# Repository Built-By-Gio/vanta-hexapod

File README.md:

# VANTA hexapod

VANTA is my 18-DOF six-legged walking robot: 6 legs with 3 MG995 servos each, printed in PLA on a Bambu A1, wired with Wago connectors and screw terminals so nothing needs soldering. It runs on an ESP32-S3 with two PCA9685 servo drivers and I drive it with an Xbox Wireless controller over Bluetooth (Bluepad32). I designed the servo caps, aluminium-horn brackets, electronics plate, hulls, top deck, riser and camera holder, and wrote the firmware, the MuJoCo simulator, the leg neural network and the assembly guide. The leg and body parts are adapted from an open-source hexapod and reworked for this build (see Credits).

Built by Gio ([Built-By-Gio](https://github.com/Built-By-Gio)).

*VANTA walking and turning on a concrete floor.* [Watch the full walking video (1:55)](media/vanta_walking.mp4)

*The v6 CAD design (Pi-era hull).*

## Status (2026-11-25)

**Done**
- VANTA is fully built and walks on the ESP32-S3 + 2x PCA9685 build, driven from an Xbox controller over Bluetooth.
- Everything in the firmware runs on the robot: tripod walking, turning, crab walking, stand/sit, body lean, height and speed control, and the wave, bow, rear-up and dance moves.
- The learned walk, the injured-leg (5-leg) walks and step climbing run on the robot. I train and develop them in the MuJoCo simulator (`4_SOFTWARE/sim_and_training/`). Full house stairs (about 18 cm) are out of reach.
- The leg neural network (`ik_net.h`) runs on the robot. On 50,000 unseen foot positions, `train_ik.py` reports about 0.5 degrees average joint error.
- The Fusion top deck, riser, camera holder and slotted tall hull (`3_CAD/deck_hull_fusion/`) are printed and on the robot.

**Not done yet**
- Camera: the holder is on the robot (Waveshare ESP32-S3-CAM, OV5640). The camera code is not written yet.
- Carrier PCB (`6_PCB_CARRIER/`): design only, not ordered. It targets the old Raspberry Pi layout.
- Raspberry Pi software (`4_SOFTWARE/hexapod-brain/`): legacy. VANTA started on a Raspberry Pi 4, and I replaced it with the ESP32-S3 before this code ran on the robot.

**Known problems**
- MG995 servos have overheated and failed: one died on the bench and was swapped. Keep a spare or two.
- The assembly guide's pictures show the +1 servo cap; the cap that fits is +2 (1 mm difference, cosmetic).
- `1_PRINT/VANTA_print_MAIN_A1.3mf` was rewritten by a script to 12 plates with +2 caps and has not been re-opened in Bambu Studio since. Check the plates before printing.
- Check the deck fit before printing the files in `3_CAD/deck_hull_fusion/`: the riser columns reach Z 59.9 mm and run 3.2 mm into the deck, and the riser opening covers the end-header servo plugs by 0.5 mm.
- Measure your camera module; the camera holder assumes a module depth of 8.5 mm.
- `3_CAD/VANTA_standing.glb` still shows an older bracket B, horn and caps. The CAD render near the top shows the v6 CAD design with the Pi-era hull, not the robot as it is today.

**Battery:** the robot runs on a 3S LiPo (stop at 10.5 V). The original parts list named a Zeee 2S 5200 mAh XT60 pack. Check that your SBEC and buck converter accept your pack's voltage.

**Still to add**
- How the ESP32-S3 board is mounted and fed 5 V (its ground goes to the 5 V- Wago).
- The script that exports `walk_net.h` (`export_walk.py`), and a note on what `best.npy` holds.

The 5:54 assembly video rendered from the CAD (337 MB) is not in this repo because of its size; its source pipeline is in `7_VIDEO/assembly_video_src/`.

## Photos

| | |
|---|---|
|  |  |
| Electronics plate during the build | Power wiring with Wago connectors |

## What you need

**Electronics and hardware** (from the 2026-11-03 parts list, `BUY_LIST.md`, with the controller changed to the current ESP32 build):

| Item | Qty |
|---|---|
| MG995 servo (plus spares) | 18 |
| ESP32-S3 DevKitC | 1 |
| PCA9685 16-channel servo driver | 2 |
| Xbox Wireless controller (Bluetooth) | 1 |
| 20 A SBEC set to 6.0 V (servo power) | 1 |
| XL4015 buck converter set to 5.1 V (logic, fans) | 1 |
| LiPo with XT60 plug (see the battery note above) | 1 |
| 20 A inline fuse, XT60 rocker switch, XT60 pigtails | 1 each |
| Wago 221 lever connectors, 16 AWG wire, F-F jumpers | as needed |
| 30 cm servo extensions | 6 |
| 30 mm 5 V fans (hull roof) | 2 |
| DaFuRui 25T aluminium disc horns (Ø20 mm, 4x M3 on a 10 mm square) | 18 |
| 623ZZ bearings (3x10x4, not flanged) | 18 |
| M3 heat-set inserts (M3 x L4 x OD5) | 44 |
| M3x6 / M3x8 / M3x10 screws | 28 (+72 for the horns) / 48 / 110 |
| M2.5x6 screws / M2x8 screws with nuts | 12 / 4 |
| Grip tape for the feet, CA glue | |

The main board and drivers need no soldering. The robot weighs about 2.45 kg with the hull (design estimate).

**Printing:** a Bambu A1 (the 3MF files are set up for it), black PLA, and optionally silver PLA with an AMS for the lettering.

**Software:**
- Arduino IDE 2 with the `esp32_bluepad32` board package 4.1.0 (board manager URL: `https://raw.githubusercontent.com/ricardoquesada/esp32-arduino-lib-builder/master/bluepad32_files/package_esp32_bluepad32_index.json`). Bluepad32 comes with this board package.
- Arduino libraries: Adafruit PWM Servo Driver Library 3.0.3 and Adafruit BusIO 1.17.4.
- For the simulator and training: Python 3.13 with `mujoco` (tested with 4.0.0) and `numpy` (tested with 2.5.3).

## How to build / run

1. **Print the fit test first.** Open `1_PRINT/VANTA_print_MAIN_A1.3mf` and print plate 1: one bracket A, one bracket B and one +2 servo cap. Build one joint (guide step 1) and check the cap fits your servo. Cap STLs from +0 to +3 are in `1_PRINT/stl_main/` if yours needs a different size.
2. **Print the rest of the MAIN file.** `1_PRINT/MAIN_plate_layout.png` shows all 12 plates. Infill: femur, tibia, both bracket As, bracket B and the caps at 15% with 4 walls; electronics plate, deck and battery mount at 10% with 2 walls; armour at 5% (it is cosmetic). The hull (`1_PRINT/VANTA_print_COLOR_AMS_A1.3mf`, or a variant from `3_CAD/deck_hull_fusion/deck_out/`) prints upright with tree supports at 10%.
3. **Assemble the mechanics** with `VANTA_assembly_guide.pdf` (rev 9, 33 pages). Each joint: a slip-on cap holds a 623ZZ bearing; an M3x10 axle self-taps through bracket A into the bearing; on the horn side, bracket B sits over the aluminium disc with 4x M3x6. Self-tap holes: drive the screw in once to cut the thread, back it out, then assemble. Wrap grip tape around the bottom 25 mm of each tibia tip as the foot. The guide's Pi wiring and Pi software chapters are legacy; use steps 4 to 8 below for the electronics.
4. **Wire the power.** Battery, switch, 20 A fuse, then a BATT+ Wago that feeds the SBEC and the buck. Both SBEC outputs (6.0 V) go to the green V+ terminals of both PCA9685 boards. The buck output (5.1 V) goes to the 5V+/5V- Wagos. PCA9685 VCC comes from the ESP32's 3.3 V. Never put servo power on a board's 5 V pin.
5. **Wire the drivers to the ESP32-S3.** Driver 1 on `Wire`: SDA GPIO 8, SCL GPIO 9. Driver 2 on `Wire1`: SDA GPIO 4, SCL GPIO 5. Both stay at address 0x40. Plug the servos in as in the table below (`BOARD`/`CH` in `vanta_hexapod_pad.ino`, lines 39-41). Leg names are from the robot's point of view, front = the way it walks with the stick forward.

   | Leg | coxa | femur | tibia |
   |---|---|---|---|
   | front left | driver 2 ch 0 | driver 2 ch 1 | driver 2 ch 2 |
   | middle left | driver 2 ch 4 | driver 2 ch 5 | driver 2 ch 3 |
   | back left | driver 2 ch 7 | driver 2 ch 6 | driver 2 ch 8 |
   | front right | driver 1 ch 0 | driver 1 ch 1 | driver 2 ch 15 |
   | middle right | driver 1 ch 3 | driver 1 ch 4 | driver 1 ch 5 |
   | back right | driver 1 ch 6 | driver 1 ch 7 | driver 1 ch 8 |

   If your wiring differs, edit `BOARD` and `CH`.
6. **Check every servo before walking.** In the Arduino IDE pick board "ESP32S3 Dev Module" and enable "USB CDC On Boot". Upload `5_ELECTRONICS_TEST/esp32s3/servo_finder/servo_finder.ino` to see which channel each servo is on (Serial Monitor 115200, "No line ending"; type `2 6` to wiggle driver 2 channel 6). Then upload `5_ELECTRONICS_TEST/esp32s3/servo_check/servo_check.ino`, which wiggles all 18 joints in order using the same table (`n` next, `b` back, `r` repeat). If the Serial Monitor shows only `ESP-ROM:`, press RST.
7. **Upload the walking firmware.** Open `4_SOFTWARE/esp32_firmware/vanta_hexapod_pad/vanta_hexapod_pad.ino` (keep `ik_net.h` and `walk_net.h` in the same folder) and upload it. Put the robot down sitting: battery on the floor, legs spread in a standing shape.
8. **Calibrate the stand pose.** In the Serial Monitor (115200, "No line ending"): `1`-`6` pick a leg, `c`/`f`/`t` pick a joint, `+`/`-` nudge 10 µs, `]`/`[` nudge 50 µs, `n` flips a joint's direction, `p` prints the `HOME_US` and `SIGN` arrays. Paste them into the sketch and upload again.
9. **Pair the controller and drive.** Put the Xbox controller in pairing mode; the ESP32 connects through Bluepad32 (`z` in the Serial Monitor forgets paired controllers). R2 stands up, L2 sits down and powers off, the Menu button turns every servo off at once. Left stick walks and crabs, right stick turns. The full control list (moves, height, speed, climb mode, injured leg, learned walk) is in the comment at the top of the sketch.

**Simulator and training** (`4_SOFTWARE/sim_and_training/`):
1. `pip install mujoco numpy`
2. `python vanta_sim.py fast` trains a population of simulated VANTAs with no window and saves the best brain to `vanta_brain.npy` in the current folder; `python vanta_sim.py` trains with a viewer; `python vanta_sim.py watch` replays the saved brain. Add a leg name (`FL ML RL FR MR RR`) to train a 5-legged walk, e.g. `python vanta_sim.py RL fast`. `vanta_brain_no_RL.npy` is a saved brain trained without the rear-left leg. The `meshes/` folder must stay next to the script.
3. `python train_ik.py` trains the leg network and writes `ik_net.h`; copy it into the firmware folder.

**CAD:** the Fusion deck script `3_CAD/deck_hull_fusion/vanta_deck_fusion.py` runs inside Fusion 360's script environment (`adsk` API). The generator scripts in `3_CAD/source/` (CadQuery/trimesh/Blender `bpy`) and `7_VIDEO/assembly_video_src/` are kept as reference for how the parts, print files and video were made. They expect a working folder layout that is not in this repo, so their paths need adjusting before they run.

## Repo layout

| Folder | What is in it |
|---|---|
| `VANTA_assembly_guide.pdf` | Assembly guide rev 9 (33 pages). Mechanical steps are current; the Pi wiring and software chapters are legacy. |
| `BUY_LIST.md` | Parts status as of 2026-11-03 (Pi-era; the controller is now the ESP32-S3). |
| `1_PRINT/` | `VANTA_print_MAIN_A1.3mf` (12 plates, +2 caps) and `MAIN_plate_layout.png`; `VANTA_print_COLOR_AMS_A1.3mf` (mech hull with silver lettering, logo letters, optional AMS base); `VANTA_one_leg_A1.3mf` (one leg on one plate, older +1 caps); STLs in `stl_main/` and `stl_color_AMS/`. |
| `3_CAD/` | `VANTA_standing.glb`, `servo_cap.step`, `stl_in_place/` (every part in the URDF frame), `source/` (generator scripts, reference only, plus `hexapod.urdf`). |
| `3_CAD/deck_hull_fusion/` | Fusion-rebuilt top deck, riser, camera holder and spacers (`deck_out/`, STL + STEP), tall-hull slot variants, modelled wire routing (`wires/`: braids, servo leads, jumpers as STEP, path data), and the Fusion scripts. The deck, riser, camera holder and slotted tall hull are on the robot. |
| `4_SOFTWARE/esp32_firmware/` | Current walking firmware `vanta_hexapod_pad` (ESP32-S3, 2x PCA9685, Bluepad32) with `ik_net.h` and `walk_net.h`. |
| `4_SOFTWARE/sim_and_training/` | MuJoCo walking simulator with meshes, the leg-network trainer, and saved brain weights. |
| `4_SOFTWARE/hexapod-brain/` | Legacy Raspberry Pi 4 software (kinematics, gait, gesture control, phone page, calibration). Not used on the current robot. |
| `5_ELECTRONICS_TEST/` | Bench tools: `servo_finder` and `servo_check` for the current ESP32 build; the one-leg test sketches and a Web Serial slider page (`servo_console.html` + `servo_console` sketches) for ESP32-S3 and Arduino Uno. |
| `6_PCB_CARRIER/` | KiCad carrier board rev A: PCB, netlist, schematic PDF, STEP, Gerbers and JLC fab files. Design only, on hold, targets the old Pi layout. There is no editable schematic file, only the netlist and PDF. |
| `7_VIDEO/assembly_video_src/` | Blender + Python pipeline for the assembly video (fonts not included; see its README). |
| `renders/` | CAD renders of the v6 robot, hull, joint and parts. |
| `media/` | Photos of the built robot, `vanta_walking.mp4` (1:55 walking video) and `vanta_walking.gif` (8-second preview). |

## Roadmap / future plans

Planned:
- **Fallen-person detection:** use the ESP32-S3 camera board to stream to a phone, show person boxes and an alert, and train a "person down / waving / OK" classifier on clips filmed from floor level.
- **Search behaviour:** scan, turn and walk toward a person the camera finds.
- **IMU self-levelling** with a BNO085 (the new top deck has a pocket for it).
- **Bus servos:** replace the MG995s, which have overheated and failed, with Waveshare ST3215 bus servos.
- **Learned walks:** add steering to the learned and injured-leg walks (they go forward and back only).

## Credits and license

- Legs, base, stiffeners, battery mount and `hexapod.urdf` are adapted from [ggldnl/Hexapod-Hardware](https://github.com/ggldnl/Hexapod-Hardware) (CERN-OHL-W-2.0). `CREDITS.md` lists exactly which files are derived and what I changed.
- Hardware design files (STL, 3MF, STEP, GLB, URDF, PCB files, assembly guide): CERN-OHL-W-2.0, see `LICENSE-HARDWARE`. The full licence text is in `CERN-OHL-W-2.0.txt`.
- Firmware and software: MIT, see `LICENSE`.
- Dependencies (not included): Bluepad32, Adafruit PWM Servo Driver, MuJoCo, NumPy; the legacy Pi software also uses OpenCV, Picamera2 and MediaPipe.

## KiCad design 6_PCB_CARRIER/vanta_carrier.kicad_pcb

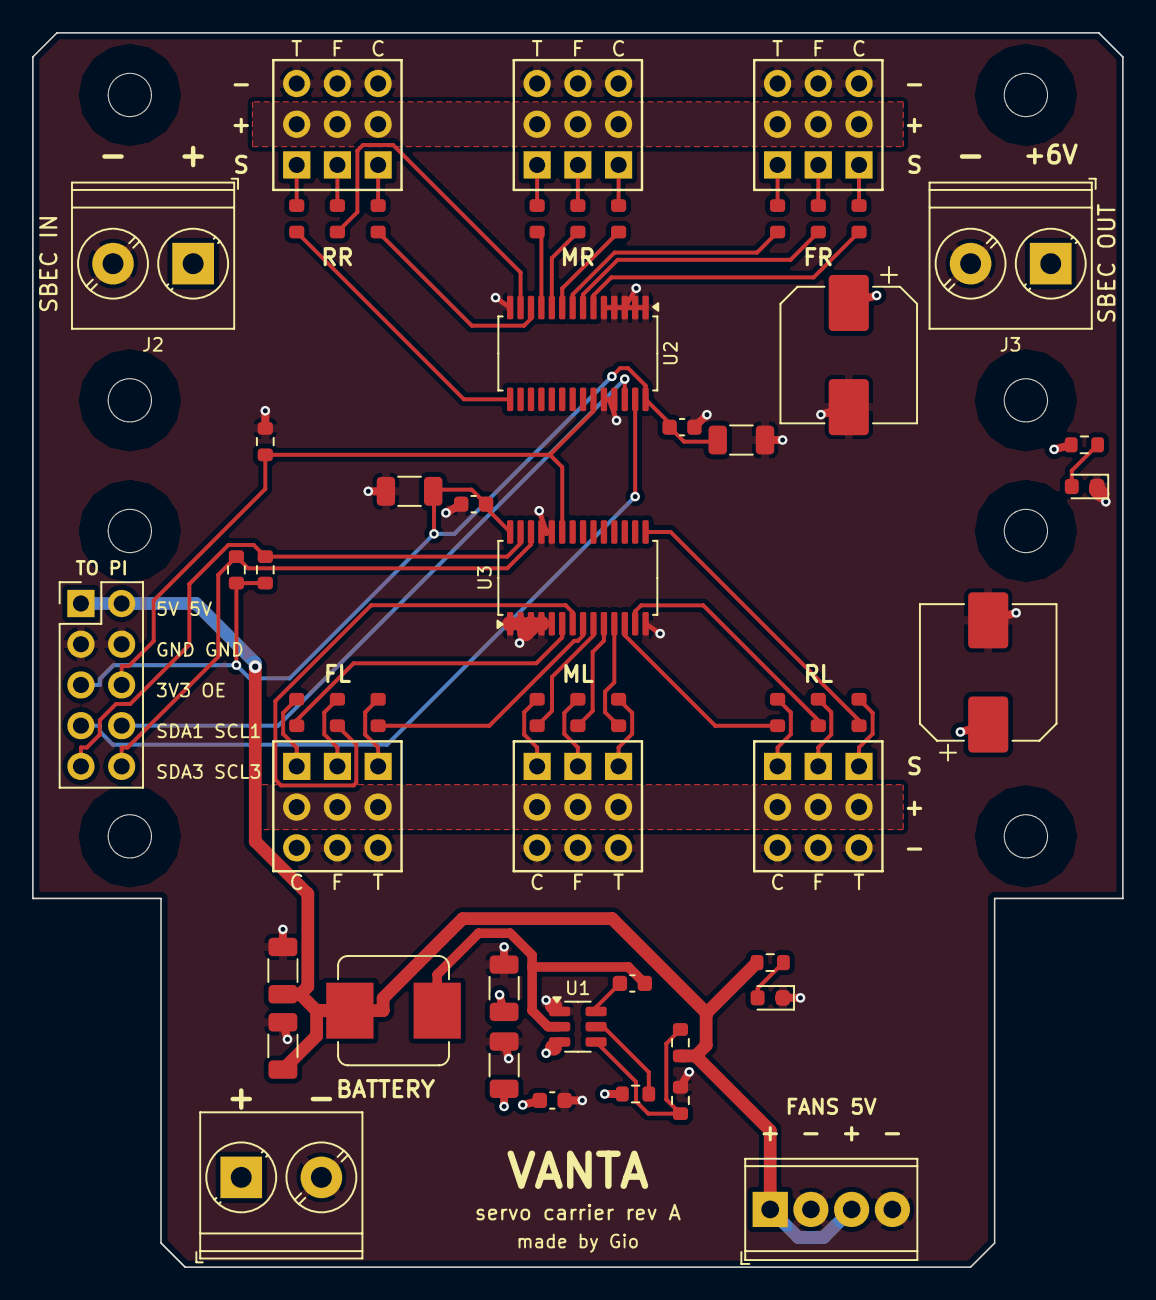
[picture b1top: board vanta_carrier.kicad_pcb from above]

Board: 4 copper layers, 68.0 x 77.0 mm, 75 parts (0 on the bottom side), 52 nets.

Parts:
C1, C2: 470 µF 16 V; CP_Elec_8x10
C3, C4: 10 µF 25 V; C_1206_3216Metric
C5: 100 nF 50 V; C_0603_1608Metric
C6, C9, C11: 100 nF; C_0603_1608Metric
C7, C8: 22 µF 10 V; C_1206_3216Metric
C10, C12: 10 µF; C_1206_3216Metric
D1: orange; LED_0603_1608Metric
D2: green; LED_0603_1608Metric
H1, H2, H3, H4, H5, H6, H7, H8: M2.5; MountingHole_2.7mm_M2.5
J1, J2, J3: PT 1,5/2-5.0-H; TerminalBlock_Phoenix_PT-1,5-2-5.0-H_1x02_P5.00mm_Horizontal
J4: MPT 0,5/4-2.54; TerminalBlock_Phoenix_MPT-0,5-4-2.54_1x04_P2.54mm_Horizontal
J6: PinHeader 2×5; PinHeader_2x05_P2.54mm_Vertical
J7: ch0 FR coxa; PinHeader_1x03_P2.54mm_Vertical
J8: ch1 FR femur; PinHeader_1x03_P2.54mm_Vertical
J9: ch2 FR tibia; PinHeader_1x03_P2.54mm_Vertical
J10: ch3 MR coxa; PinHeader_1x03_P2.54mm_Vertical
J11: ch4 MR femur; PinHeader_1x03_P2.54mm_Vertical
J12: ch5 MR tibia; PinHeader_1x03_P2.54mm_Vertical
J13: ch6 RR coxa; PinHeader_1x03_P2.54mm_Vertical
J14: ch7 RR femur; PinHeader_1x03_P2.54mm_Vertical
J15: ch8 RR tibia; PinHeader_1x03_P2.54mm_Vertical
J16: ch0 FL coxa; PinHeader_1x03_P2.54mm_Vertical
J17: ch1 FL femur; PinHeader_1x03_P2.54mm_Vertical
J18: ch2 FL tibia; PinHeader_1x03_P2.54mm_Vertical
J19: ch3 ML coxa; PinHeader_1x03_P2.54mm_Vertical
J20: ch4 ML femur; PinHeader_1x03_P2.54mm_Vertical
J21: ch5 ML tibia; PinHeader_1x03_P2.54mm_Vertical
J22: ch6 RL coxa; PinHeader_1x03_P2.54mm_Vertical
J23: ch7 RL femur; PinHeader_1x03_P2.54mm_Vertical
J24: ch8 RL tibia; PinHeader_1x03_P2.54mm_Vertical
L1: 3.3 µH; L_Bourns_SRP7028A_7.3x6.6mm
R1, R5: 1 kΩ; R_0603_1608Metric
R2: 100 kΩ; R_0603_1608Metric
R3: 56.2 kΩ 1%; R_0603_1608Metric
R4: 10 kΩ 1%; R_0603_1608Metric
R6, R7: 4.7 kΩ; R_0603_1608Metric
R8: 10 kΩ; R_0603_1608Metric
R9, R10, R11, R12, R13, R14, R15, R16, R17, R18, R19, R20, R21, R22, R23, R24, R25, R26: 220 Ω; R_0603_1608Metric
U1: TPS563201DDC; TSOT-23-6
U2, U3: PCA9685PW; TSSOP-28_4.4x9.7mm_P0.65mm

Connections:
+3V3: C9.1, C10.1, C11.1, C12.1, J6.5, R6.1, R7.1, U2.28, U3.28
+5V: C7.1, C8.1, J4.1, J4.3, J6.1, J6.2, L1.2, R3.1, R5.1
BST: C6.1, U1.6
EN_5V: R2.2, U1.5
FB: R3.2, R4.1, U1.4
FL_COXA: J16.1, R18.2
FL_FEMUR: J17.1, R19.2
FL_TIBIA: J18.1, R20.2
FR_COXA: J7.1, R9.2
FR_FEMUR: J8.1, R10.2
FR_TIBIA: J9.1, R11.2
GND: C1.2, C2.2, C3.2, C4.2, C5.2, C7.2, C8.2, C9.2, C10.2, C11.2, C12.2, D1.1, D2.1, J1.2, J2.2, J3.2, J4.2, J4.4, J6.3, J6.4, J7.3, J8.3, J9.3, J10.3, J11.3, J12.3, J13.3, J14.3, J15.3, J16.3, J17.3, J18.3, J19.3, J20.3, J21.3, J22.3, J23.3, J24.3, R4.2, R8.2, U1.1, U2.1, U2.2, U2.3, U2.4, U2.5, U2.14, U2.24, U2.25, U3.1, U3.2, U3.3, U3.4, U3.5, U3.14, U3.24, U3.25
LED_5V: D2.2, R5.2
LED_SERVO: D1.2, R1.2
ML_COXA: J19.1, R21.2
ML_FEMUR: J20.1, R22.2
ML_TIBIA: J21.1, R23.2
MR_COXA: J10.1, R12.2
MR_FEMUR: J11.1, R13.2
MR_TIBIA: J12.1, R14.2
RL_COXA: J22.1, R24.2
RL_FEMUR: J23.1, R25.2
RL_TIBIA: J24.1, R26.2
RR_COXA: J13.1, R15.2
RR_FEMUR: J14.1, R16.2
RR_TIBIA: J15.1, R17.2
SCL1: J6.8, U2.26
SCL3: J6.10, R7.2, U3.26
SDA1: J6.7, U2.27
SDA3: J6.9, R6.2, U3.27
SERVO_OE: J6.6, R8.1, U2.23, U3.23
SW: C6.2, L1.1, U1.2
U2_LED0: R9.1, U2.6
U2_LED1: R10.1, U2.7
U2_LED2: R11.1, U2.8
U2_LED3: R12.1, U2.9
U2_LED4: R13.1, U2.10
U2_LED5: R14.1, U2.11
U2_LED6: R15.1, U2.12
U2_LED7: R16.1, U2.13
U2_LED8: R17.1, U2.15
U3_LED0: R18.1, U3.6
U3_LED1: R19.1, U3.7
U3_LED2: R20.1, U3.8
U3_LED3: R21.1, U3.9
U3_LED4: R22.1, U3.10
U3_LED5: R23.1, U3.11
U3_LED6: R24.1, U3.12
U3_LED7: R25.1, U3.13
U3_LED8: R26.1, U3.15
VBAT: C3.1, C4.1, C5.1, J1.1, J2.1, R2.1, U1.3
V_SERVO: C1.1, C2.1, J3.1, J7.2, J8.2, J9.2, J10.2, J11.2, J12.2, J13.2, J14.2, J15.2, J16.2, J17.2, J18.2, J19.2, J20.2, J21.2, J22.2, J23.2, J24.2, R1.1
